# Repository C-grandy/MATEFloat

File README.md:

# MATEFloat
A PCB and code for a Ranger class MATE 2024 float 
NOTE: This design should not be recreated, for reference only as it has errors 

## PCB
The PCB is based around a Atmel Atmega328p MCU interfacing with a HC-5 Bluetooth module, brushed motor driver IC, and a pressure sensor. The PCB's main purpose is to take commands over bluetooth and then dive to the bottom of a pool, find the depth, and then return to the surface and transmit the data from the pressure sensor. All electrical aspects of this system worked well, but unfortunately due to mechanical design errors the system was never tested in full capacity. 

### Power and Motor driver
The PCB features independent 3.3V and 5V linear regulators to step down a supply from two 9V batteries in parallel. The motor driver, a TI DRV8220DRLR, is powered straight from the 9V supply. The motor driver is interfaced with the MCU using two control pins, each getting proportional control via PWM. 

### Control and Communications
The system is based around a Atmel Atmega328p as it allowed for both backup software written in Arduino C++ and bare metal C for most use cases. The MCU is interfaced with a HC05 bluetooth module for communication as it was both affordable and easy to communicate to over serial UART. The float also incorporates a analog input for a pressure sensor for depth determination. A simple logic level shifter consisting of two signal MOSFETs were also included as the MCU and bluetooth module operate at different voltage levels. 

## Code
The system is programmed in AVR bare metal C, incorporating a custom made UART hardware abstraction layer (HAL) for easier to understand code. The code at its current state doesn't fully incorporate sensor readings or transmitting, but simple bluetooth communication is established. 
NOTE: The code is not at a finished state, some features work but there is limited documentation, for reference only.

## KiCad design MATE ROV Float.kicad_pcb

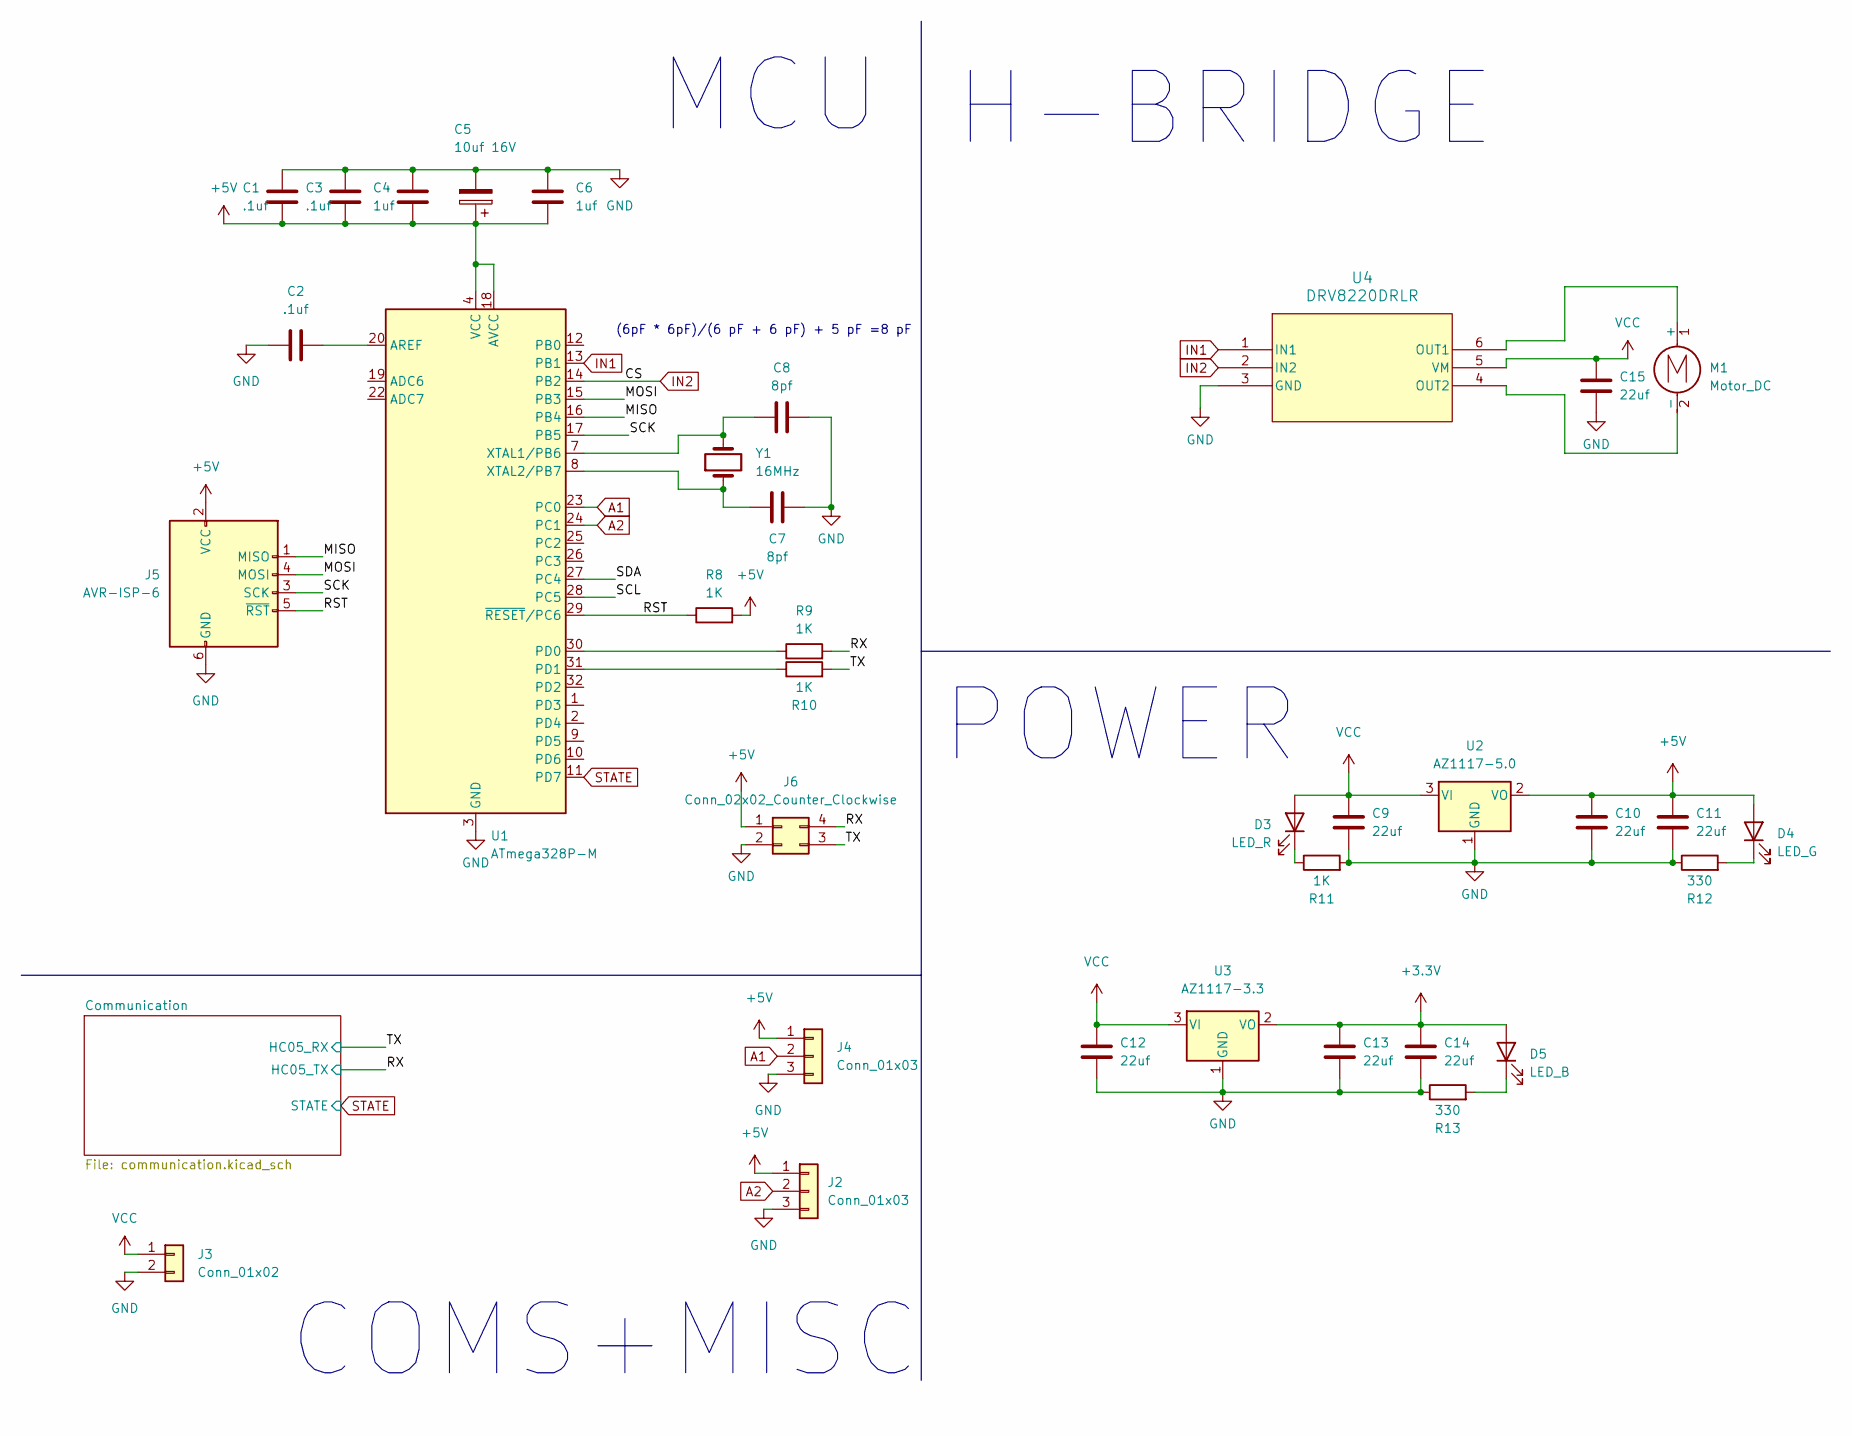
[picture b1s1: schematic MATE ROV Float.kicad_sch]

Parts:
C1, C2, C3: .1uf; C_0603_1608Metric_Pad1.08x0.95mm_HandSolder
C4, C6: 1uf; C_0603_1608Metric_Pad1.08x0.95mm_HandSolder
C5: 10uf 16V
C7, C8: 8pf; C_0603_1608Metric_Pad1.08x0.95mm_HandSolder
C9, C10, C11, C12, C13, C14, C15: 22uf; C_0603_1608Metric_Pad1.08x0.95mm_HandSolder
D3: LED_R; LED_0603_1608Metric_Pad1.05x0.95mm_HandSolder
D4: LED_G; LED_0603_1608Metric_Pad1.05x0.95mm_HandSolder
D5: LED_B; LED_0603_1608Metric_Pad1.05x0.95mm_HandSolder
J2, J4: Conn_01x03; JST_XH_B3B-XH-A_1x03_P2.50mm_Vertical
J3: Conn_01x02; JST_XH_B2B-XH-A_1x02_P2.50mm_Vertical
J5: AVR-ISP-6; IDC-Header_2x03_P2.54mm_Vertical
J6: Conn_02x02_Counter_Clockwise; PinHeader_2x02_P2.54mm_Vertical
M1: Motor_DC; JST_XH_B2B-XH-A_1x02_P2.50mm_Vertical
R8, R9, R10, R11: 1K; R_0603_1608Metric_Pad0.98x0.95mm_HandSolder
R12, R13: 330; R_0603_1608Metric_Pad0.98x0.95mm_HandSolder
U1: ATmega328P-M; QFN-32-1EP_5x5mm_P0.5mm_EP3.1x3.1mm
U2: AZ1117-5.0; SOT-223-3_TabPin2
U3: AZ1117-3.3; SOT-223-3_TabPin2
U4: DRV8220DRLR; SOT-563
Y1: 16MHz; Crystal_SMD_EuroQuartz_MT-4Pin_3.2x2.5mm; Part # RH100-16.000-8-2020-TR

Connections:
+3.3V: C13.1, C14.1, D5.2 (A), U3.2 (VO); also elsewhere on the board
+5V: C1.2, C3.2, C4.2, C5.1, C6.2, C10.1, C11.1, D4.2 (A), J2.1, J4.1, J5.2 (VCC), J6.1, R8.2, U1.4 (VCC), U1.6 (VCC), U1.18 (AVCC), U2.2 (VO); also elsewhere on the board
/MISO: J5.1 (MISO), U1.16 (PB4)
/MOSI: J5.4 (MOSI), U1.15 (PB3)
/RST: J5.5 (~RST), R8.1, U1.29 (~RESET/PC6)
/RX: J6.4, R9.2; also elsewhere on the board
/SCK: J5.3 (SCK), U1.17 (PB5)
/SCL: U1.28 (PC5)
/SDA: U1.27 (PC4)
/TX: J6.3, R10.2; also elsewhere on the board
A1: J4.2, U1.23 (PC0)
A2: J2.2, U1.24 (PC1)
GND: C1.1, C2.1, C3.1, C4.1, C5.2, C6.1, C7.1, C8.1, C9.2, C10.2, C11.2, C12.2, C13.2, C14.2, C15.2, J2.3, J3.2, J4.3, J5.6 (GND), J6.2, R11.2, R12.1, R13.1, U1.3 (GND), U1.5 (GND), U1.21 (GND), U1.33 (GND), U2.1 (GND), U3.1 (GND), U4.3 (GND); also elsewhere on the board
IN1: U1.13 (PB1), U4.1 (IN1)
IN2: U1.14 (PB2), U4.2 (IN2)
unnamed: D3.1 (K), R11.1
unnamed: D4.1 (K), R12.2
unnamed: D5.1 (K), R13.2
unnamed: M1.1 (+), U4.6 (OUT1)
unnamed: M1.2 (-), U4.4 (OUT2)
unnamed: C2.2, U1.20 (AREF)
unnamed: R9.1, U1.30 (PD0)
unnamed: R10.1, U1.31 (PD1)
unnamed: C8.2, U1.7 (XTAL1/PB6), Y1.2
unnamed: C7.2, U1.8 (XTAL2/PB7), Y1.1
STATE: U1.11 (PD7); also elsewhere on the board
VCC: C9.1, C12.1, C15.1, D3.2 (A), J3.1, U2.3 (VI), U3.3 (VI), U4.5 (VM)

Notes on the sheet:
POWER
COMS+MISC
MCU
(6pF * 6pF)/(6 pF + 6 pF) + 5 pF =8 pF
H-BRIDGE

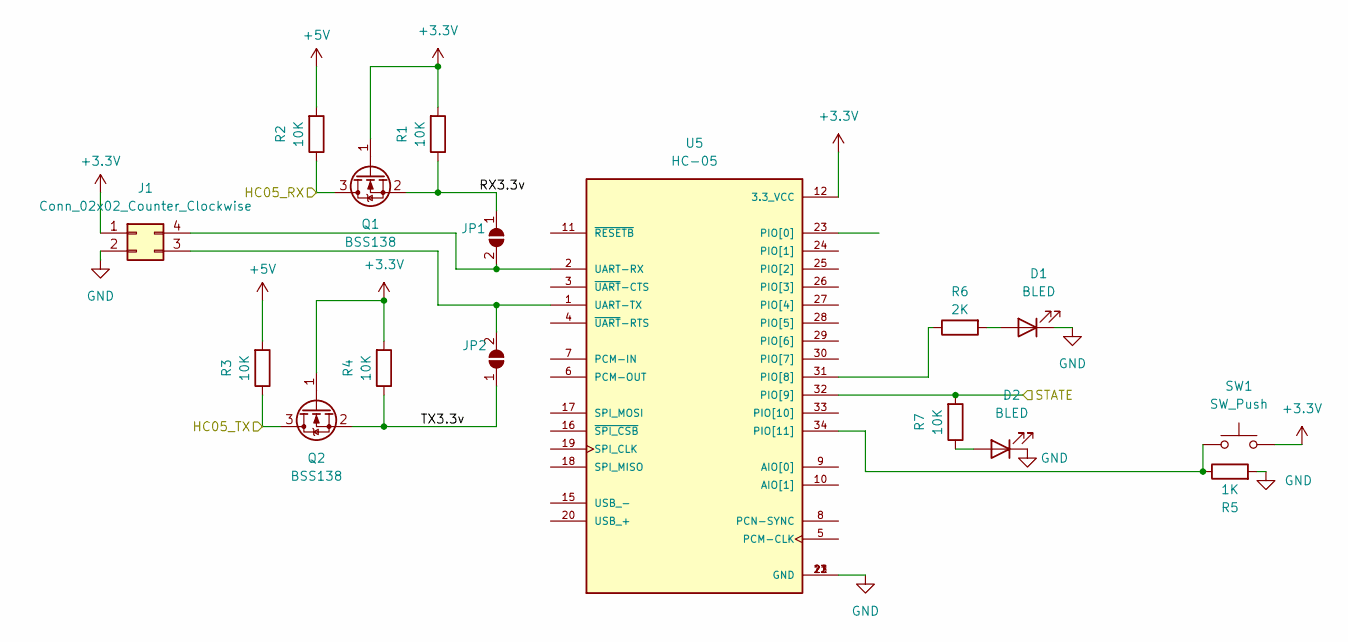
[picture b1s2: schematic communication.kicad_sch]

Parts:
D1, D2: BLED; LED_0603_1608Metric_Pad1.05x0.95mm_HandSolder
J1: Conn_02x02_Counter_Clockwise; PinHeader_2x02_P2.54mm_Vertical
JP1, JP2: SolderJumper_2_Open; SolderJumper-2_P1.3mm_Open_RoundedPad1.0x1.5mm
Q1, Q2: BSS138; SOT-23
R1, R2, R3, R4, R7: 10K; R_0603_1608Metric_Pad0.98x0.95mm_HandSolder
R5: 1K; R_0603_1608Metric_Pad0.98x0.95mm_HandSolder
R6: 2K; R_0603_1608Metric_Pad0.98x0.95mm_HandSolder
SW1: SW_Push; PTS526
U5: HC-05; XCVR_HC-05; PARTREV v1.0

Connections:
+3.3V: J1.1, Q1.1 (G), Q2.1 (G), R1.2, R4.2, SW1.2, U5.12 (3.3_VCC); also elsewhere on the board
+5V: R2.2, R3.2; also elsewhere on the board
/Communication /RX3.3v: JP1.1 (A), Q1.2 (S), R1.1
/Communication /TX3.3v: JP2.1 (A), Q2.2 (S), R4.1
/RX: Q2.3 (D), R3.1; also elsewhere on the board
/TX: Q1.3 (D), R2.1; also elsewhere on the board
GND: D1.1 (K), D2.1 (K), J1.2, R5.2, U5.13 (GND), U5.21 (GND), U5.22 (GND); also elsewhere on the board
unnamed: D1.2 (A), R6.2
unnamed: D2.2 (A), R7.1
unnamed: J1.3, JP2.2 (B), U5.1 (UART-TX)
unnamed: J1.4, JP1.2 (B), U5.2 (UART-RX)
unnamed: R6.1, U5.31 (PIO[8])
unnamed: R5.1, SW1.1, U5.34 (PIO[11])
STATE: R7.2, U5.32 (PIO[9]); also elsewhere on the board

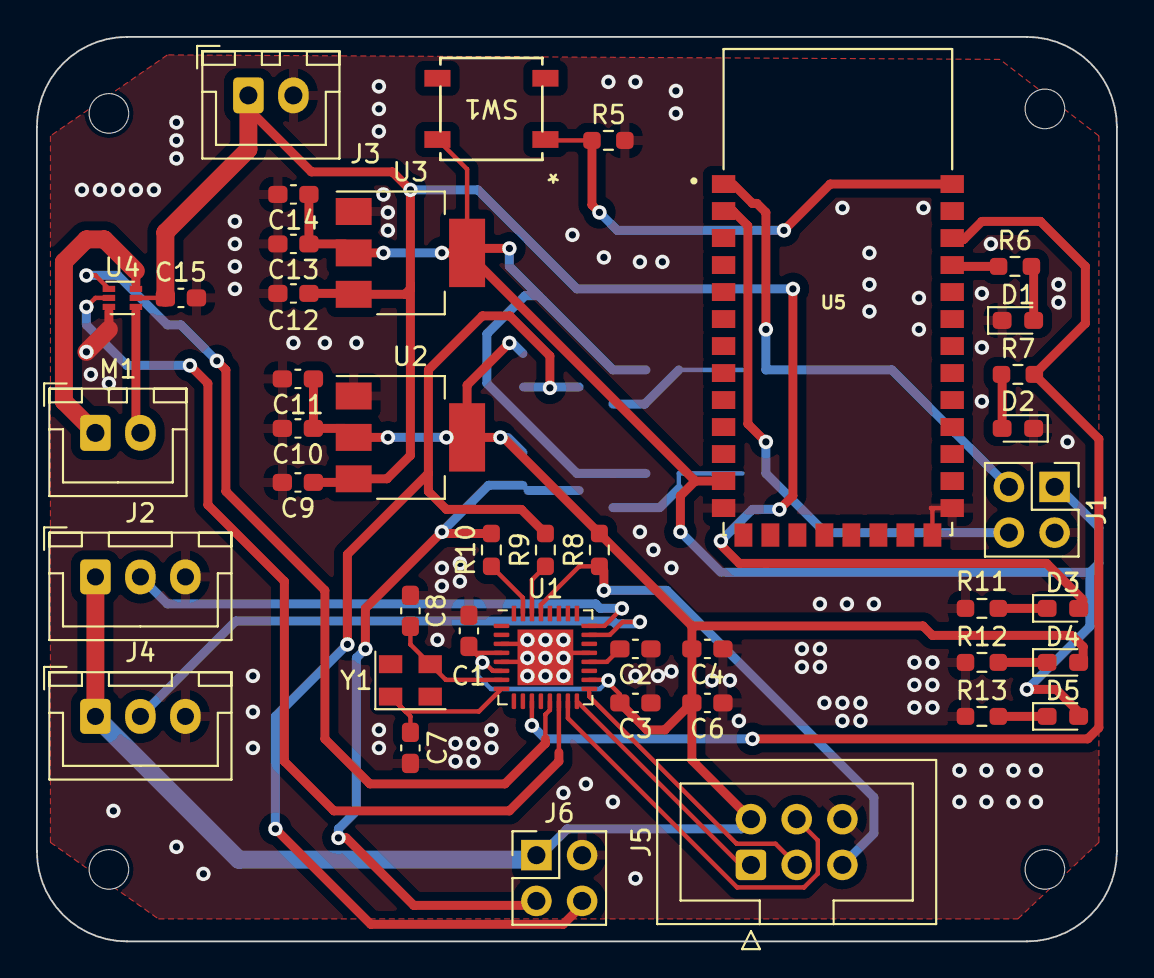
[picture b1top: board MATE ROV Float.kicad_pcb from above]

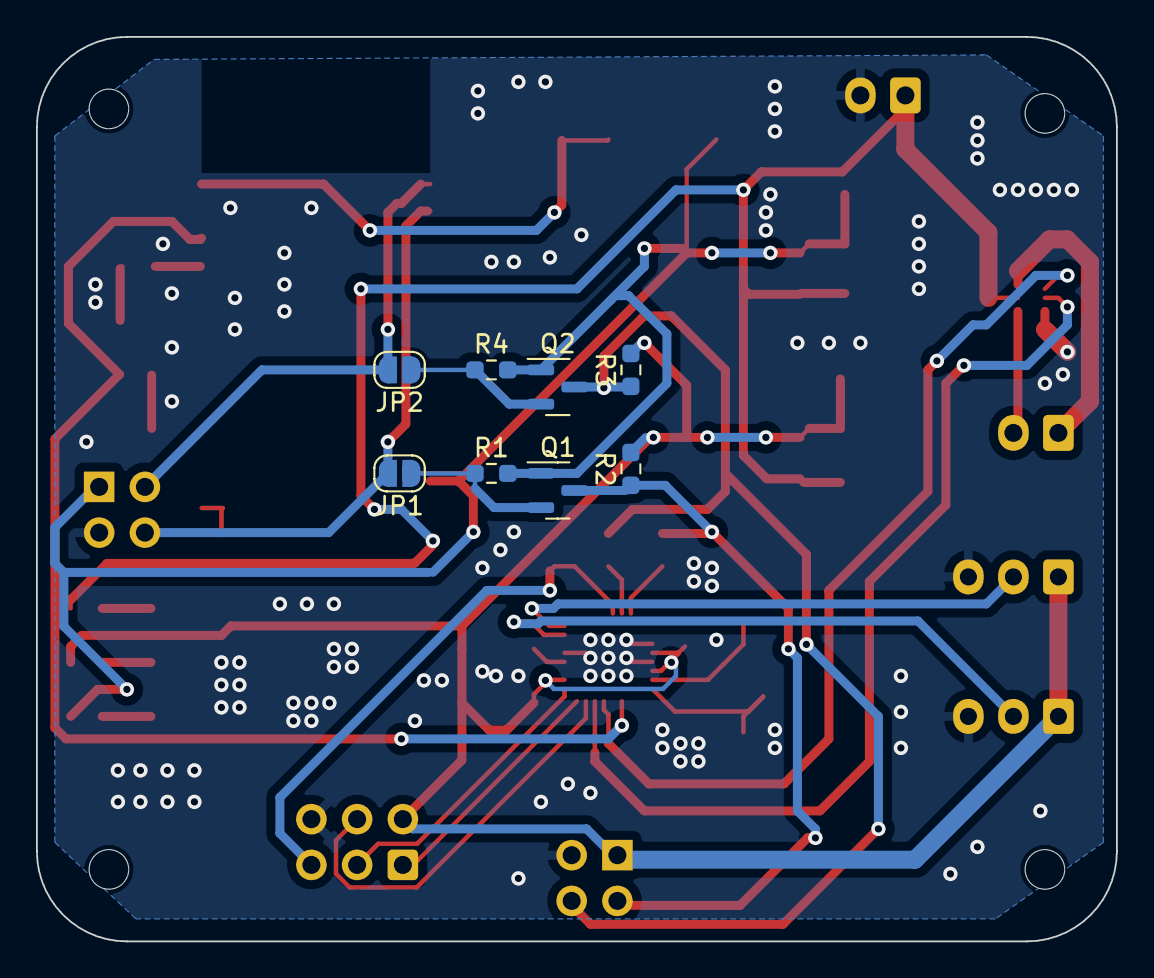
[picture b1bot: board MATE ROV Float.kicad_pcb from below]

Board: 2 copper layers, 60.0 x 50.2 mm, 50 parts (8 on the bottom side), 33 nets.

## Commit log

2025-09-18 Rename MATE ROV Float.kicad_prl to PCB/MATE ROV Float.kicad_prl
2025-09-18 Rename MATE ROV Float.kicad_pro to PCB/MATE ROV Float.kicad_pro
2025-09-18 Rename MATE ROV Float.step to PCB/MATE ROV Float.step
2025-09-18 Update and rename fp-info-cache to PCB/fp-info-cache
2025-09-18 Rename ~MATE ROV Float.kicad_pcb.lck to PCB/~MATE ROV Float.kicad_pcb.lck
2025-09-18 Rename ~MATE ROV Float.kicad_sch.lck to PCB/~MATE ROV Float.kicad_sch.lck
2025-09-18 Create A
